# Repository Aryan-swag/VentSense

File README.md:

# VentSense — Multimodal Early Vent-Gas & Thermal-Runaway Cell Isolation

**Vishwakarma Awards 2026-27** · Sustainable Energy track (mentor: IIT Hyderabad) · Application ID `VK26-IITH-SE-0279`
Team VentSense, IIT (BHU) Varanasi

VentSense is a low-cost safety add-on for small Li-ion packs. Every cell segment is watched by three dissimilar signals: vent gas (MQ-7 for CO, MQ-8 for H2), cell-wall temperature (DS18B20) and voltage sag relative to the neighbouring cells (ADS1115). An ESP32 runs 2-of-3 voting. When two signal types trip on the same cell within a 60–120 s window, that cell's fail-secure SPDT bypass relay drops and the other cells keep powering the load. If two or more cells trip, the pack relay opens.

Our claim is narrow: **2-of-3 voting across dissimilar signals plus per-cell isolation, as a low-cost retrofit for small packs.** Gas-based and voltage-based battery monitoring both exist already as prior art.

## Repository map

| What | Status | Path |
| :--- | :--- | :--- |
| KiCad 10 project (6 hierarchical sheets, 136 symbols) | ERC: 0 errors, 0 warnings (default checks) | [`kicad/VentSense_Stage2/`](kicad/VentSense_Stage2/) |
| **Controller carrier PCB v1.1 (for fabrication)** | DRC: 0 violations, 0 unconnected, 0 parity issues (default checks, `--schematic-parity`) | [`PCB/`](PCB/) (ordering guide: [`PCB/ORDERING.md`](PCB/ORDERING.md)) |
| Gerber + Excellon package v1.1 | 2 layers, 124 × 126 mm | [`PCB/fabrication/VentSense_Carrier_Gerbers_v1.1.zip`](PCB/fabrication/VentSense_Carrier_Gerbers_v1.1.zip) |
| Stage 2 exports (schematic PDF/PNG, ERC/DRC, BOM CSV) | as submitted at Stage 2 (Oct 2026) | [`exports/`](exports/) |
| Bill of materials | Rev 2.1 Final | [`bom/`](bom/) |
| Mechanical CAD (SolidWorks) and wax thermal study | | [`ventsense_cad/`](ventsense_cad/) |
| Controller firmware (ESP32, PlatformIO) | 39/39 unit tests pass; Wi-Fi dashboard, IR test, health indicator, relay self-check; both ESP32 builds compile (hardware bring-up pending) | [`firmware/`](firmware/) (feature plan: [`firmware/FEATURES.md`](firmware/FEATURES.md)) |
| Digital twin (software-in-the-loop simulation) | 35/35 scenario checks; 0/40 false trips; 40/40 failing cells isolated; IR test within 2 % | [`sim/`](sim/) (results: [`sim/out/summary.md`](sim/out/summary.md)) |
| Superseded v1.0 PCB outputs | archived, do not order | [`PCB/archive_v1.0/`](PCB/archive_v1.0/) |

## Schematic sheets

1. **Power:** 12 V input, IRF4905 reverse-polarity protection, heater branch (5 A fuse, E-stop NC2, KSD301 70 °C cutoff), TC4427 gate driver, IRLZ44N switches.
2. **Pack_Path:** 4S INR18650-25R string, 4 SPDT bypass relays, pack relay (COM→NO), E-stop NC1, 3 A fuse, INA219, XT60, 10 Ω load.
3. **Measurement:** 100 k/20 k cell dividers into ADS1115 #3 (0x4B); 15 k/22 k gas dividers into ADS1115 #1 (0x48, CO) and #2 (0x49, H2); DS18B20 1-Wire bus.
4. **MCU_IO:** ESP32-DevKitC-32E, OLED, BME280, DS3231 RTC, microSD, MAX6675, 2 × PCF8574 status LEDs, buzzer, buttons.
5. **Connectors:** the carrier board's off-board connectors and solder jumpers (added in v1.1).

## Controller carrier PCB v1.1

- 2-layer FR-4, 1.6 mm, 1 oz copper. 124 × 126 mm, 4 × M3 holes. Minimum track and gap 0.2 mm, minimum drill 0.4 mm (vias), via annular ring 0.2 mm.
- Logic and signal currents only. Heater, load and pack currents stay off this board.
- Screw terminals (5.08 mm): `+12V`, gate outputs to the off-board IRLZ44Ns, cell taps (≤ 16.8 V, kept on their own connector), and `+5V` from the XL4015, with 100 µF + 100 nF at the input.
- Headers for the 4-channel relay module, the pack relay module and the INA219.
- Plug-in sockets for the ESP32-DevKitC (rows 25.40 mm apart, per Espressif's DevKitC V4 drawing) and the 3 ADS1115 modules. The other modules use labelled sockets wired with jumper leads.
- Net-class track widths: `+5V` 1.0 mm, `+3V3`/`GND`/`RLY_VCC` 0.5 mm, `+12V` 0.4 mm (TC4427 supply only), signals 0.25 mm. GND pours on both layers, stitched with vias.
- **JP1 (relay module VCC):** 1-2 = `+5V` (default), 2-3 = `+3V3`.
- **JP2 (MAX6675 SO):** 1-2 = shared SPI MISO (IO19, default), 2-3 = IO36. This is the fallback if the microSD module doesn't release MISO.

All PCB files (Gerbers, drill files, BOM, reports, renders) and the ordering note are in [`PCB/`](PCB/).

## Firmware and simulation

- **Safety core** ([`firmware/lib/safety_core`](firmware/lib/safety_core)): hardware-free C++. It covers:
  - 2-of-3 voting across gas, temperature and voltage, with a 90 s correlation window;
  - Level 1/2/3 latching, cleared only by the physical reset;
  - room-gas (common-mode) rejection, rate-of-rise triggers and sensor-fault detection;
  - relay verification and heater limits.
- **The same source runs in three places:** on the ESP32, in the native unit tests, and inside the digital twin.
- **Digital twin** ([`sim/`](sim/)): models the cells, wax jacket, vent gas, sensors and heater rig, with the real safety core in the loop.
  - Fault profiles and model parameters are **assumed** (tagged in `sim/params.py`).
  - The results show the firmware logic and timing behave as designed against modelled faults. They are not measurements on real cells.

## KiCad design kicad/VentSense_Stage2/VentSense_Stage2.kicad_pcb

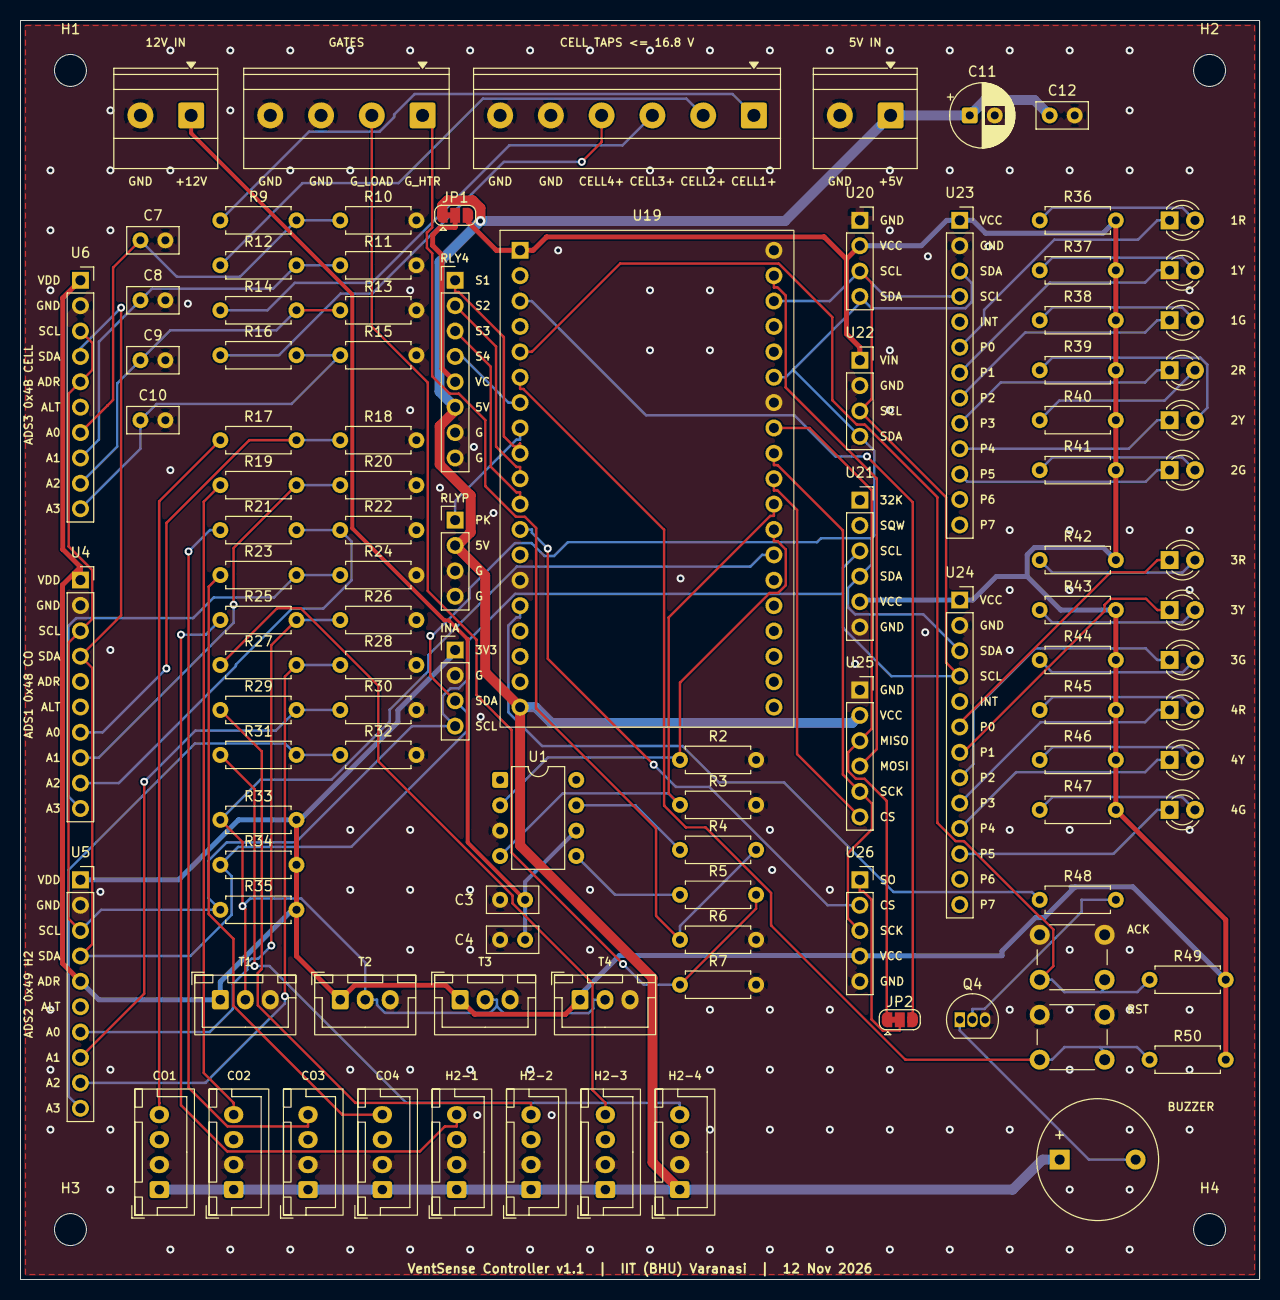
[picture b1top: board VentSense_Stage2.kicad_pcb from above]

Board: 2 copper layers, 124.0 x 126.0 mm, 109 parts (0 on the bottom side), 79 nets.

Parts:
BZ1: 5V active buzzer; Buzzer_12x9.5RM7.6
C3: 1uF; C_Disc_D5.0mm_W2.5mm_P2.50mm
C4: 0.1uF; C_Disc_D5.0mm_W2.5mm_P2.50mm
C7, C8, C9, C10, C12: 100nF; C_Disc_D5.0mm_W2.5mm_P2.50mm
C11: 100uF; CP_Radial_D6.3mm_P2.50mm
D2: Seg 1 Red; LED_D3.0mm
D3: Seg 1 Yellow; LED_D3.0mm
D4: Seg 1 Green; LED_D3.0mm
D5: Seg 2 Yellow; LED_D3.0mm
D6: Seg 2 Red; LED_D3.0mm
D7: Seg 2 Green; LED_D3.0mm
D8: Seg 3 Red; LED_D3.0mm
D9: Seg 3 Yellow; LED_D3.0mm
D10: Seg 3 Green; LED_D3.0mm
D11: Seg 4 Red; LED_D3.0mm
D12: Seg 4 Yellow; LED_D3.0mm
D13: Seg 4 Green; LED_D3.0mm
H1, H2, H3, H4: M3; MountingHole_3.2mm_M3
J3: J_5V_IN (from XL4015); TerminalBlock_Phoenix_MKDS-1,5-2-5.08_1x02_P5.08mm_Horizont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
J4: J_12V_IN (protected +12V); TerminalBlock_Phoenix_MKDS-1,5-2-5.08_1x02_P5.08mm_Horizont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
J5: J_CELL (cell + taps); TerminalBlock_Phoenix_MKDS-1,5-6-5.08_1x06_P5.08mm_Horizont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
J6: J_RLY_SEG (4-ch relay module); PinHeader_1x08_P2.54mm_Vertical
J7: J_RLY_PACK (1-ch relay module); PinHeader_1x04_P2.54mm_Vertical
J8: J_GATE (to off-board IRLZ44N); TerminalBlock_Phoenix_MKDS-1,5-4-5.08_1x04_P5.08mm_Horizont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
J9: J_I2C_EXT (INA219); PinHeader_1x04_P2.54mm_Vertical
JP1: Relay VCC: 1-2 +5V (default), 2-3 +3V3; SolderJumper-3_P1.3mm_Bridged12_RoundedPad1.0x1.5mm
JP2: MAX6675 SO: 1-2 SPI_MISO (default), 2-3 GPIO36; SolderJumper-3_P1.3mm_Bridged12_RoundedPad1.0x1.5mm
Q4: BC547; TO-92_Inline
R2, R3, R6, R7: 100k; R_Axial_DIN0207_L6.3mm_D2.5mm_P7.62mm_Horizontal
R4, R5: 10; R_Axial_DIN0207_L6.3mm_D2.5mm_P7.62mm_Horizontal
R9, R12, R14, R16: 100k 1%; R_Axial_DIN0207_L6.3mm_D2.5mm_P7.62mm_Horizontal
R10, R11, R13, R15: 20k 1%; R_Axial_DIN0207_L6.3mm_D2.5mm_P7.62mm_Horizontal
R17, R19, R21, R23, R25, R27, R29, R31: 15k; R_Axial_DIN0207_L6.3mm_D2.5mm_P7.62mm_Horizontal
R18, R20, R22, R24, R26, R28, R30, R32: 22k; R_Axial_DIN0207_L6.3mm_D2.5mm_P7.62mm_Horizontal
R33: 4.7 kΩ; R_Axial_DIN0207_L6.3mm_D2.5mm_P7.62mm_Horizontal
R34, R35: 4.7k; R_Axial_DIN0207_L6.3mm_D2.5mm_P7.62mm_Horizontal
R36, R37, R38, R39, R40, R41, R42, R43, R44, R45, R46, R47: 330; R_Axial_DIN0207_L6.3mm_D2.5mm_P7.62mm_Horizontal
R48: 1k; R_Axial_DIN0207_L6.3mm_D2.5mm_P7.62mm_Horizontal
R49, R50: 10k; R_Axial_DIN0207_L6.3mm_D2.5mm_P7.62mm_Horizontal
SW1: Acknowledge; SW_PUSH_6mm
SW2: Reset; SW_PUSH_6mm
U1: TC4427 (DIP-8); DIP-8_W7.62mm
U4: ADS1115 #1 0x48 (CO); PinSocket_1x10_P2.54mm_Vertical
U5: ADS1115 #2 0x49 (H2); PinSocket_1x10_P2.54mm_Vertical
U6: ADS1115 #3 0x4B (cells); PinSocket_1x10_P2.54mm_Vertical
U7: MQ-7 seg 1; JST_XH_B4B-XH-A_1x04_P2.50mm_Vertical
U8: MQ-7 seg 2; JST_XH_B4B-XH-A_1x04_P2.50mm_Vertical
U9: MQ-7 seg 3; JST_XH_B4B-XH-A_1x04_P2.50mm_Vertical
U10: MQ-7 seg 4; JST_XH_B4B-XH-A_1x04_P2.50mm_Vertical
U11: MQ-8 seg 1; JST_XH_B4B-XH-A_1x04_P2.50mm_Vertical
U12: MQ-8 seg 2; JST_XH_B4B-XH-A_1x04_P2.50mm_Vertical
U13: MQ-8 seg 3; JST_XH_B4B-XH-A_1x04_P2.50mm_Vertical
U14: MQ-8 seg 4; JST_XH_B4B-XH-A_1x04_P2.50mm_Vertical
U15: DS18B20 cell 1; JST_XH_B3B-XH-A_1x03_P2.50mm_Vertical
U16: DS18B20 cell 2; JST_XH_B3B-XH-A_1x03_P2.50mm_Vertical
U17: DS18B20 cell 3; JST_XH_B3B-XH-A_1x03_P2.50mm_Vertical
U18: DS18B20 cell 4; JST_XH_B3B-XH-A_1x03_P2.50mm_Vertical
U19: ESP32-DevKitC-32E; ESP32-DevKitC-32E_2x19_P2.54mm_W25.4mm
U20: OLED 0x3C; PinSocket_1x04_P2.54mm_Vertical
U21: DS3231 RTC 0x68; PinSocket_1x06_P2.54mm_Vertical
U22: BME280 0x76; PinSocket_1x04_P2.54mm_Vertical
U23: PCF8574 #1 0x20; PinSocket_1x13_P2.54mm_Vertical
U24: PCF8574 #2 0x21; PinSocket_1x13_P2.54mm_Vertical
U25: microSD; PinSocket_1x06_P2.54mm_Vertical
U26: MAX6675; PinSocket_1x05_P2.54mm_Vertical

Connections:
+3V3: J9.1, JP1.3, R33.2, R34.2, R35.2, R36.2, R37.2, R38.2, R39.2, R40.2, R41.2, R42.2, R43.2, R44.2, R45.2, R46.2, R47.2, R49.2, R50.2, U4.1 (VDD), U5.1 (VDD), U5.5 (ADDR), U6.1 (VDD), U15.1 (VDD), U16.1 (VDD), U17.1 (VDD), U18.1 (VDD), U19.1 (3V3), U20.2 (VCC), U21.5 (VCC), U22.1 (VIN), U23.1 (VCC), U24.1 (VCC), U26.4
+5V: BZ1.1 (+), C11.1, C12.1, J3.1, J6.6, J7.2, JP1.1, U7.1 (VCC), U8.1 (VCC), U9.1 (VCC), U10.1 (VCC), U11.1 (VCC), U12.1 (VCC), U13.1 (VCC), U14.1 (VCC), U19.19 (5V), U25.2 (VCC)
+12V: C3.2, C4.2, J4.1, U1.6 (V_{DD})
/MCU_IO/BTN_ACK: R49.1, SW1.1, U19.5 (IO34)
/MCU_IO/BTN_RST: R50.1, SW2.1, U19.6 (IO35)
/MCU_IO/BUZZER: R48.1, U19.15 (IO13)
/MCU_IO/SD_CS: U19.29 (IO5), U25.6 (CS)
/MCU_IO/SPI_MISO: JP2.1, U19.27 (IO19), U25.3 (MISO)
/MCU_IO/SPI_MOSI: U19.21 (IO23), U25.4 (MOSI)
/MCU_IO/SPI_SCK: U19.28 (IO18), U25.5 (SCK), U26.3
/MCU_IO/TC_CS: U19.12 (IO14), U26.2
/MCU_IO/TC_SO: JP2.2, U26.1
/MCU_IO/TC_SO_ALT: JP2.3, U19.3 (IO36/VP)
/Measurement/GAS1_CO: R17.2, R18.1, U4.7 (A0)
/Measurement/GAS1_H2: R25.2, R26.1, U5.7 (A0)
/Measurement/GAS2_CO: R19.2, R20.1, U4.8 (A1)
/Measurement/GAS2_H2: R29.2, R30.1, U5.8 (A1)
/Measurement/GAS3_CO: R21.2, R22.1, U4.9 (A2)
/Measurement/GAS3_H2: R27.2, R28.1, U5.9 (A2)
/Measurement/GAS4_CO: R23.2, R24.1, U4.10 (A3)
/Measurement/GAS4_H2: R31.2, R32.1, U5.10 (A3)
/Measurement/VSENS1: C7.1, R9.2, R10.1, U6.7 (A0)
/Measurement/VSENS2: C8.1, R11.1, R12.2, U6.8 (A1)
/Measurement/VSENS3: C9.1, R13.1, R14.2, U6.9 (A2)
/Measurement/VSENS4: C10.1, R15.1, R16.2, U6.10 (A3)
CELL1_P: J5.1, R9.1
CELL2_P: J5.2, R12.1
CELL3_P: J5.3, R14.1
CELL4_P: J5.4, R16.1
GATE_HTR: J8.1, R4.2, R6.1
GATE_LOAD: J8.2, R5.2, R7.1
GND: C3.1, C4.1, C7.2, C8.2, C9.2, C10.2, C11.2, C12.2, J3.2, J4.2, J5.5, J5.6, J6.7, J6.8, J7.3, J7.4, J8.3, J8.4, J9.2, Q4.3 (E), R2.2, R3.2, R6.2, R7.2, R10.2, R11.2, R13.2, R15.2, R18.2, R20.2, R22.2, R24.2, R26.2, R28.2, R30.2, R32.2, SW1.2, SW2.2, U1.3 (GND), U4.2 (GND), U4.5 (ADDR), U5.2 (GND), U6.2 (GND), U7.2 (GND), U8.2 (GND), U9.2 (GND), U10.2 (GND), U11.2 (GND), U12.2 (GND), U13.2 (GND), U14.2 (GND), U15.3 (GND), U16.3 (GND), U17.3 (GND), U18.3 (GND), U19.14 (GND), U19.20 (GND), U19.26 (GND), U20.1 (GND), U21.6 (GND), U22.2 (GND), U23.2 (GND), U24.2 (GND), U25.1 (GND), U26.5
HTR_EN: R2.1, U1.2 (IN_A), U19.31 (IO16)
LOAD_EN: R3.1, U1.4 (IN_B), U19.30 (IO17)
unnamed: BZ1.2 (-), Q4.1 (C)
unnamed: D2.2 (A), R36.1
unnamed: D2.1 (K), U23.6 (P0)
unnamed: D3.2 (A), R37.1
unnamed: D3.1 (K), U23.7 (P1)
unnamed: D4.2 (A), R38.1
unnamed: D4.1 (K), U23.8 (P2)
unnamed: D5.2 (A), R39.1
unnamed: D5.1 (K), U23.10 (P4)
unnamed: D6.2 (A), R40.1
unnamed: D6.1 (K), U23.9 (P3)
unnamed: D7.2 (A), R41.1
unnamed: D7.1 (K), U23.11 (P5)
unnamed: D8.2 (A), R42.1
unnamed: D8.1 (K), U24.6 (P0)
unnamed: D9.2 (A), R43.1
unnamed: D9.1 (K), U24.7 (P1)
unnamed: D10.2 (A), R44.1
unnamed: D10.1 (K), U24.8 (P2)
unnamed: D11.2 (A), R45.1
unnamed: D11.1 (K), U24.9 (P3)
unnamed: D12.2 (A), R46.1
unnamed: D12.1 (K), U24.10 (P4)
unnamed: D13.2 (A), R47.1
unnamed: D13.1 (K), U24.11 (P5)
unnamed: Q4.2 (B), R48.2
unnamed: R4.1, U1.7 (OUT_A)
unnamed: R5.1, U1.5 (OUT_B)
unnamed: R17.1, U7.4 (AO)
unnamed: R19.1, U8.4 (AO)
unnamed: R21.1, U9.4 (AO)
unnamed: R23.1, U10.4 (AO)
unnamed: R25.1, U11.4 (AO)
unnamed: R29.1, U12.4 (AO)
unnamed: R27.1, U13.4 (AO)
unnamed: R31.1, U14.4 (AO)
ONEWIRE: R33.1, U15.2 (DQ), U16.2 (DQ), U17.2 (DQ), U18.2 (DQ), U19.32 (IO4)
RLY_PACK: J7.1, U19.8 (IO33)
RLY_SEG1: J6.1, U19.9 (IO25)
RLY_SEG2: J6.2, U19.10 (IO26)
RLY_SEG3: J6.3, U19.11 (IO27)
RLY_SEG4: J6.4, U19.7 (IO32)
RLY_VCC: J6.5, JP1.2
SCL: J9.4, R35.1, U4.3 (SCL), U5.3 (SCL), U6.3 (SCL), U6.5 (ADDR), U19.22 (IO22), U20.3 (SCL), U21.3 (SCL), U22.3 (SCL), U23.4 (SCL), U24.4 (SCL)
SDA: J9.3, R34.1, U4.4 (SDA), U5.4 (SDA), U6.4 (SDA), U19.25 (IO21), U20.4 (SDA), U21.4 (SDA), U22.4 (SDA), U23.3 (SDA), U24.3 (SDA)

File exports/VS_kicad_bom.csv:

"Refs","Value","Footprint","Qty","DNP"
"BT1","INR18650-25R","","1",""
"BT2","INR18650-25R","","1",""
"BT3","INR18650-25R","","1",""
"BT4","INR18650-25R","","1",""
"BZ1","5V active buzzer","","1",""
"C1","1000uF 25V","","1",""
"C2","1000uF 25V","","1",""
"C3","1uF","Package_SO:SOIC-8_3.9x4.9mm_P1.27mm","1",""
"C4","0.1uF","","1",""
"C5","100uF","","1",""
"C6","0.1uF","","1",""
"C7","100nF","","1",""
"C8","100nF","","1",""
"C9","100nF","","1",""
"C10","100nF","","1",""
"D1","1N4742A 12V","","1",""
"D2","Seg 1 Red","Package_DIP:DIP-8_W7.62mm","1",""
"D3","Seg 1 Yellow","Package_DIP:DIP-8_W7.62mm","1",""
"D4","Seg 1 Green","Package_DIP:DIP-8_W7.62mm","1",""
"D5","Seg 2 Yellow","Package_DIP:DIP-8_W7.62mm","1",""
"D6","Seg 2 Red","Package_DIP:DIP-8_W7.62mm","1",""
"D7","Seg 2 Green","Package_DIP:DIP-8_W7.62mm","1",""
"D8","Seg 3 Red","Package_DIP:DIP-8_W7.62mm","1",""
"D9","Seg 3 Yellow","Package_DIP:DIP-8_W7.62mm","1",""
"D10","Seg 3 Green","Package_DIP:DIP-8_W7.62mm","1",""
"D11","Seg 4 Red","Package_DIP:DIP-8_W7.62mm","1",""
"D12","Seg 4 Yellow","Package_DIP:DIP-8_W7.62mm","1",""
"D13","Seg 4 Green","Package_DIP:DIP-8_W7.62mm","1",""
"F1","5A fast 5x20","","1",""
"F2","MF-R250 2.5A hold","","1",""
"F3","MF-R250 2.5A hold","","1",""
"F4","MF-R250 2.5A hold","","1",""
"F5","MF-R250 2.5A hold","","1",""
"F6","3A fast 5x20","","1",""
"HT1","12V 40W cartridge","","1",""
"J1","DC jack 5.5x2.1 ≥5A","","1",""
"J2","XT60 (load)","","1",""
"K1","4ch relay SRD-05VDC-SL-C","","1",""
"K2","1ch relay (pack)","","1",""
"Q1","IRF4905","Package_TO_SOT_THT:TO-220-3_Vertical","1",""
"Q2","IRLZ44N","Package_TO_SOT_THT:TO-220-3_Vertical","1",""
"Q3","IRLZ44N","Package_TO_SOT_THT:TO-220-3_Vertical","1",""
"Q4","BC547","Package_TO_SOT_THT:TO-92_Inline","1",""
"R1","10k","Package_TO_SOT_THT:TO-220-3_Vertical","1",""
"R2","100k","Package_TO_SOT_THT:TO-220-3_Vertical","1",""
"R3","100k","","1",""
"R4","10","","1",""
"R5","10","","1",""
"R6","100k","","1",""
"R7","100k","","1",""
"R8","10R 50W","","1",""
"R9","100k 1%","","1",""
"R10","20k 1%","","1",""
"R11","20k 1%","","1",""
"R12","100k 1%","","1",""
"R13","20k 1%","","1",""
"R14","100k 1%","","1",""
"R15","20k 1%","","1",""
"R16","100k 1%","","1",""
"R17","15k","","1",""
"R18","22k","","1",""
"R19","15k","","1",""
"R20","22k","","1",""
"R21","15k","","1",""
"R22","22k","","1",""
"R23","15k","","1",""
"R24","22k","","1",""
"R25","15k","","1",""
"R26","22k","","1",""
"R27","15k","","1",""
"R28","22k","","1",""
"R29","15k","","1",""
"R30","22k","","1",""
"R31","15k","","1",""
"R32","22k","","1",""
"R33","4.7 kΩ","","1",""
"R34","4.7k","","1","DNP"
"R35","4.7k","","1","DNP"
"R36","330","","1",""
"R37","330","","1",""
"R38","330","","1",""
"R39","330","","1",""
"R40","330","","1",""
"R41","330","","1",""
"R42","330","","1",""
"R43","330","","1",""
"R44","330","","1",""
"R45","330","","1",""
"R46","330","","1",""
"R47","330","","1",""
"R48","1k","Package_TO_SOT_THT:TO-92_Inline","1",""
"R49","10k","Package_TO_SOT_THT:TO-92_Inline","1",""
"R50","10k","Package_TO_SOT_THT:TO-92_Inline","1",""
"S1","E-stop 2NC","","1",""
"SW1","Acknowledge","","1",""
"SW2","Reset","","1",""
"TS1","KSD301 70°C NC","","1",""
"U1","TC4427 (DIP-8)","Package_SO:SOIC-8_3.9x4.9mm_P1.27mm","1",""
"U2","XL4015 set 5.0V","Package_TO_SOT_THT:TO-220-3_Vertical","1",""
"U3","INA219 0x40","","1",""
"U4","ADS1115 #1 0x48 (CO)","","1",""
"U5","ADS1115 #2 0x49 (H2)","","1",""
"U6","ADS1115 #3 0x4B (cells)","","1",""
"U7","MQ-7 seg 1","","1",""
"U8","MQ-7 seg 2","","1",""
"U9","MQ-7 seg 3","","1",""
"U10","MQ-7 seg 4","","1",""
"U11","MQ-8 seg 1","","1",""
"U12","MQ-8 seg 2","","1",""
"U13","MQ-8 seg 3","","1",""
"U14","MQ-8 seg 4","","1",""
"U15","DS18B20 cell 1","","1",""
"U16","DS18B20 cell 2","","1",""
"U17","DS18B20 cell 3","","1",""
"U18","DS18B20 cell 4","","1",""
"U19","ESP32-DevKitC-32E","","1",""
"U20","OLED 0x3C","","1",""
"U21","DS3231 RTC 0x68","","1",""
"U22","BME280 0x76","","1",""
"U23","PCF8574 #1 0x20","","1",""
"U24","PCF8574 #2 0x21","","1",""
"U25","microSD","","1",""
"U26","MAX6675","","1",""

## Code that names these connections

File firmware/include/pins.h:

// ESP32-DevKitC-32E pin map: source of truth is design spec section 5.4 / 5.5.
#pragma once

// I2C bus (ADS1115 x3, INA219, BME280, DS3231, SSD1306, PCF8574 x2)
#define PIN_SDA 21
#define PIN_SCL 22
// 1-Wire (4 x DS18B20, 4.7k pull-up R33 on the carrier)
#define PIN_ONEWIRE 4
// SPI: microSD + MAX6675 share SCK/MISO
#define PIN_SPI_SCK 18
#define PIN_SPI_MISO 19
#define PIN_SPI_MOSI 23
#define PIN_SD_CS 5
#define PIN_TC_CS 14
#define PIN_TC_SO_ALT 36  // only if JP2 is moved to 2-3 (MAX6675 SO -> IO36)

// Relays: active-HIGH (decision 41, H trigger). HIGH = energised = cell in string.
// High-Z at reset (no pull), so the relays stay released during boot.
#define PIN_RLY_SEG1 25
#define PIN_RLY_SEG2 26
#define PIN_RLY_SEG3 27
#define PIN_RLY_SEG4 32
#define PIN_RLY_PACK 33

// TC4427 gate-driver inputs (100k pull-downs R2/R3 on the carrier)
#define PIN_HTR_EN 16
#define PIN_LOAD_EN 17

// UI
#define PIN_BUZZER 13   // BC547 low side, 5 V active buzzer
#define PIN_BTN_ACK 34  // input-only, external 10k pull-up, pressed = LOW
#define PIN_BTN_RST 35  // input-only, external 10k pull-up, pressed = LOW

// I2C addresses (design spec 5.5)
#define I2C_ADS_CO 0x48    // ADS1115 #1, ADDR -> GND, MQ-7 x4
#define I2C_ADS_H2 0x49    // ADS1115 #2, ADDR -> VDD, MQ-8 x4
#define I2C_ADS_CELL 0x4B  // ADS1115 #3, ADDR -> SCL, cell taps (divider 100k/20k = 1/6)
#define I2C_INA219 0x40
#define I2C_BME280 0x76
#define I2C_DS3231 0x68
#define I2C_OLED 0x3C
#define I2C_PCF_1 0x20  // LEDs segments 1-2
#define I2C_PCF_2 0x21  // LEDs segments 3-4

static const int PIN_RLY_SEG[4] = {PIN_RLY_SEG1, PIN_RLY_SEG2, PIN_RLY_SEG3, PIN_RLY_SEG4};
